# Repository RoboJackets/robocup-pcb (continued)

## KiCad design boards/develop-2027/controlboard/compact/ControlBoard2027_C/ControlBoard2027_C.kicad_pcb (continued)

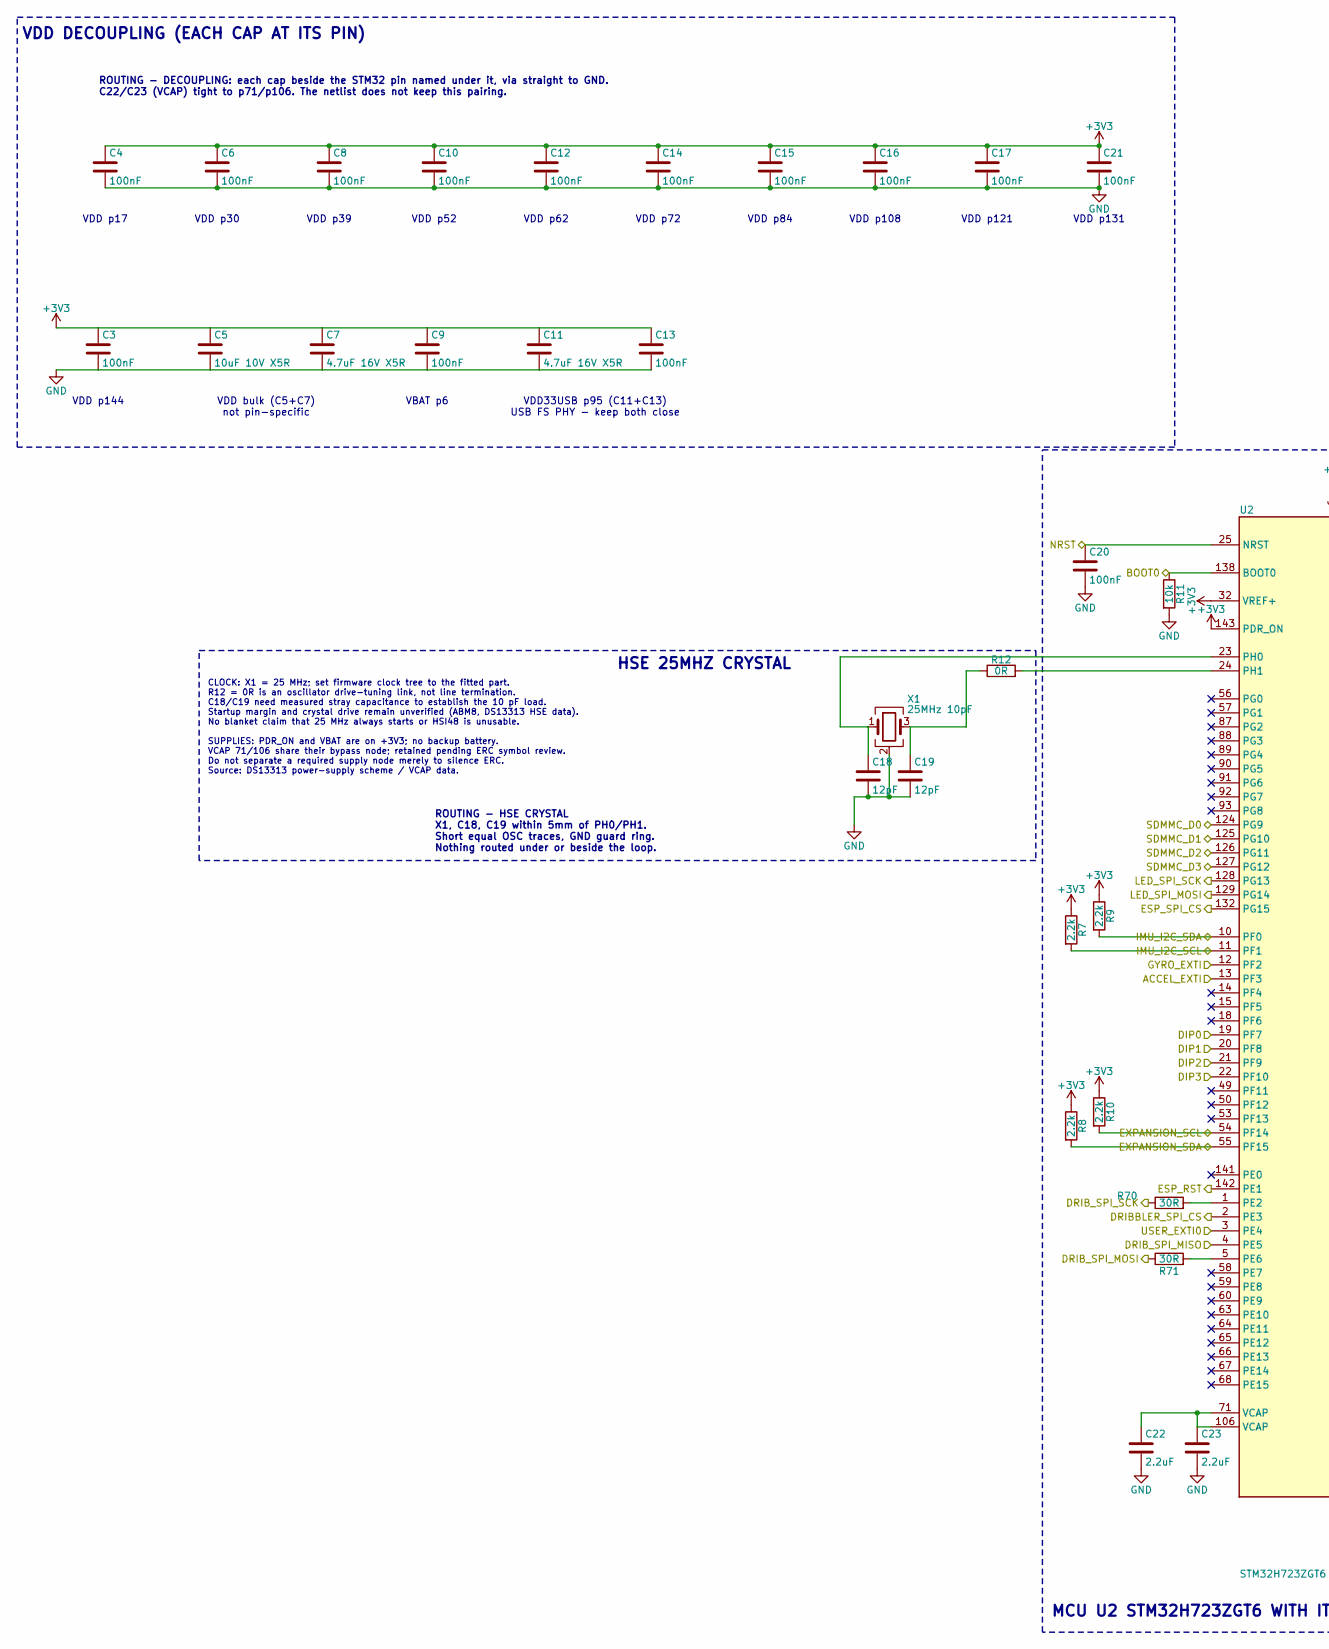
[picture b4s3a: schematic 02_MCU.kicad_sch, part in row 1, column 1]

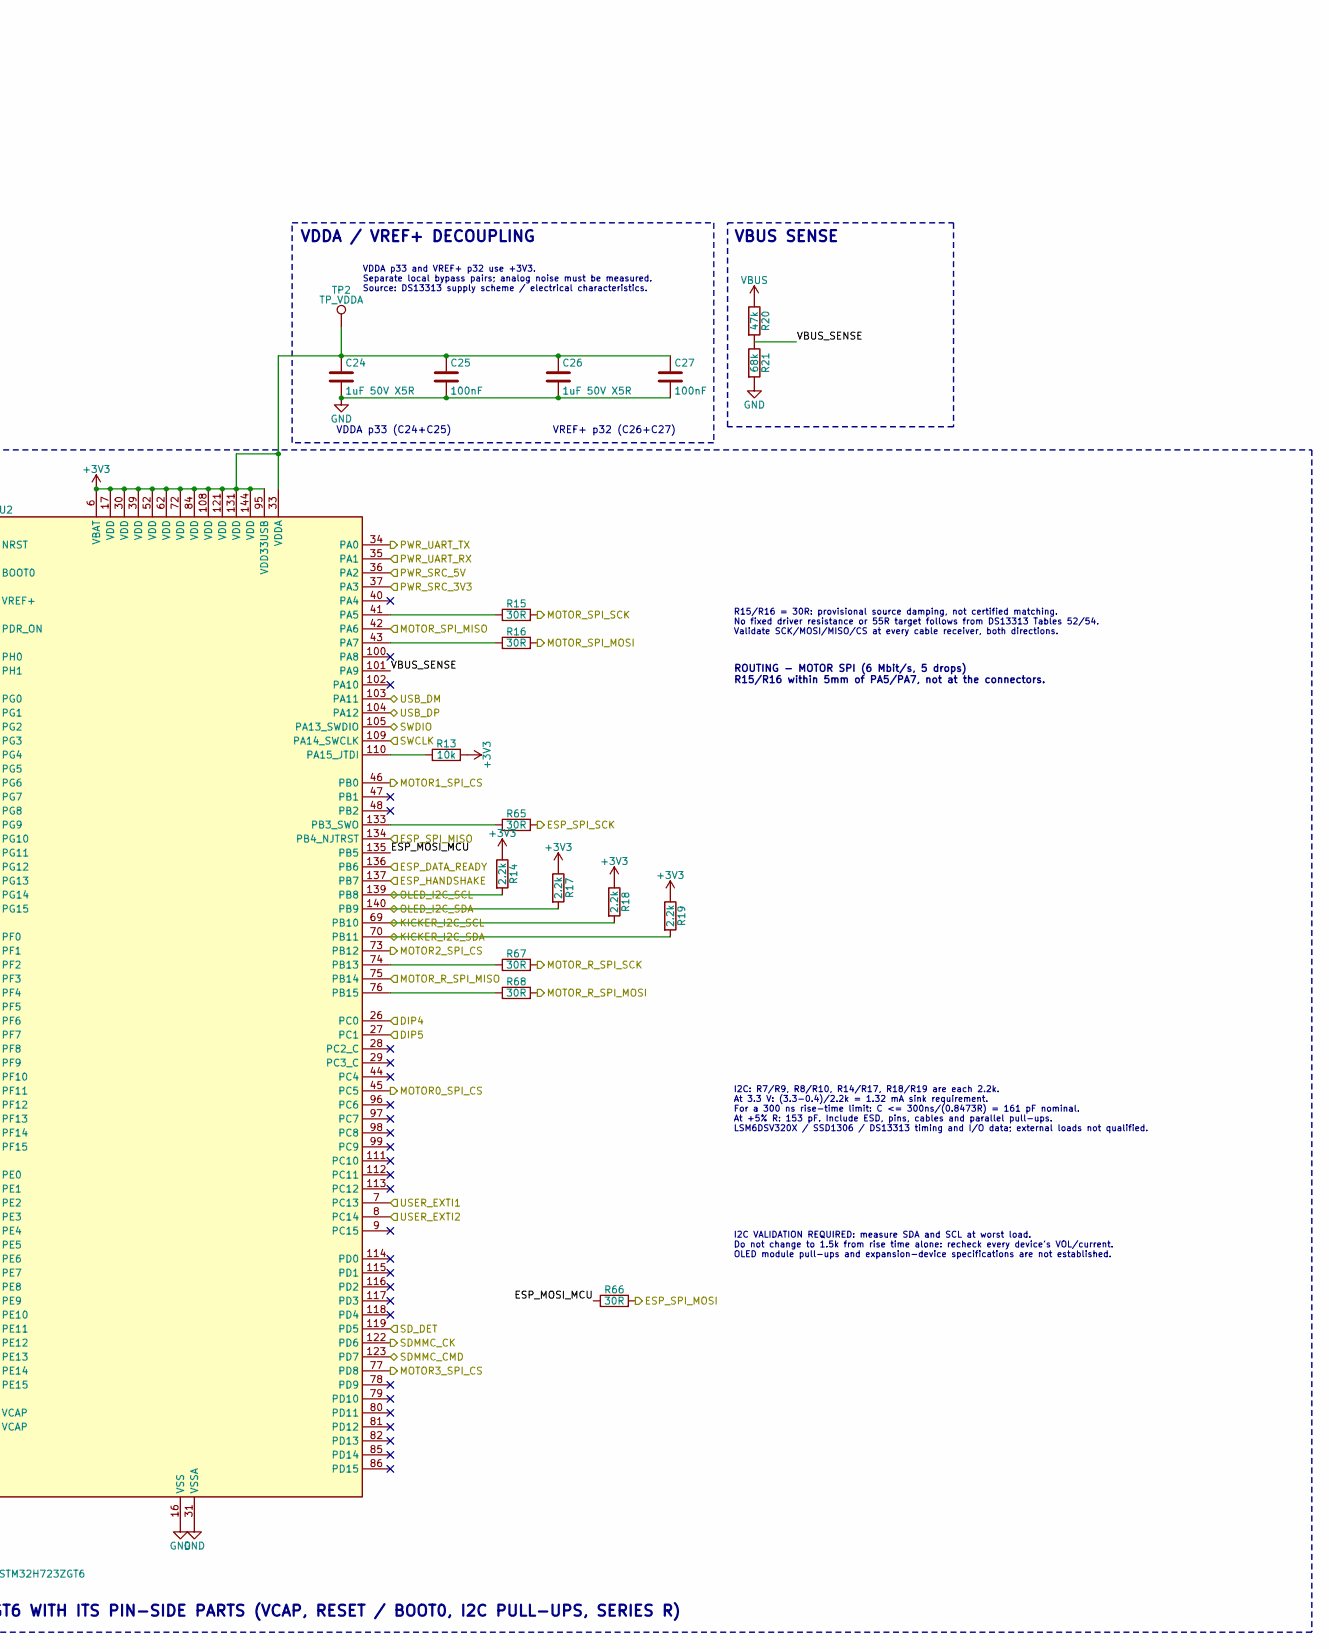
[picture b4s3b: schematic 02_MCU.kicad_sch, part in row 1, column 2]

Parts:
C3, C4, C6, C8, C9, C10, C12, C13, C14, C15, C16, C17, C20, C21, C25, C27: 100nF; C_0402_1005Metric; Rating 16V X7R; MPN Samsung CL05B104KO5NNNC; LCSC C1525
C5: 10uF 10V X5R; C_0603_1608Metric; Rating 10V X5R 10%; MPN Taiyo Yuden LMK107BBJ106MALT; LCSC C19702
C7, C11: 4.7uF 16V X5R; C_0603_1608Metric; Rating 16V X5R; MPN TDK C1608X5R1C475K080AC; LCSC C19666
C18, C19: 12pF; C_0402_1005Metric; Rating 50V C0G; MPN Samsung CL05C120JB5NNNC; LCSC C1547
C22, C23: 2.2uF; C_0603_1608Metric; Rating 10V X7R; MPN Samsung CL10B225KP8NNNC; LCSC C100082
C24, C26: 1uF 50V X5R; C_0603_1608Metric; Rating 50V X5R; MPN Samsung CL10A105KP8NNNC; LCSC C15849
R7, R8, R9, R10, R14, R17, R18, R19: 2.2k; R_0402_1005Metric; Rating 1%; MPN Yageo RC0402FR-072K2L; LCSC C25879
R11, R13: 10k; R_0402_1005Metric; Rating 1%; MPN Yageo RC0402FR-0710KL; LCSC C25744
R12: 0R; R_0402_1005Metric; Rating 0R jumper; MPN Stackpole RMCF0402ZT0R00; LCSC C17168
R15, R16, R65, R66, R67, R68, R70, R71: 30R; R_0402_1005Metric; Rating 1%; MPN Stackpole RMCF0402FT30R0; LCSC C2479340
R20: 47k; R_0402_1005Metric; Rating 1%; MPN Yageo RC0402FR-0747KL; LCSC C25792
R21: 68k; R_0402_1005Metric; Rating 1%; MPN Vishay CRCW040268K0FKED; LCSC C482226
TP2: TP_VDDA; TestPoint_Pad_1.5x1.5mm
U2: STM32H723ZGT6; LQFP-144_20x20mm_P0.5mm; MPN ST STM32H723ZGT6; LCSC C730146
X1: 25MHz 10pF; Crystal_SMD_3225-4Pin_3.2x2.5mm; MPN Abracon ABM8-25.000MHZ-10-B1U-T; LCSC C5366868

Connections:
+3V3: C3.1, C4.1, C5.1, C6.1, C7.1, C8.1, C9.1, C10.1, C11.1, C12.1, C13.1, C14.1, C15.1, C16.1, C17.1, C21.1, C24.1, C25.1, C26.1, C27.1, R7.1, R8.1, R9.1, R10.1, R13.2, R14.1, R17.1, R18.1, R19.1, TP2.1 (1_1), U2.6 (VBAT), U2.17 (VDD), U2.30 (VDD), U2.32 (VREF+), U2.33 (VDDA), U2.39 (VDD), U2.52 (VDD), U2.62 (VDD), U2.72 (VDD), U2.84 (VDD), U2.95 (VDD33USB), U2.108 (VDD), U2.121 (VDD), U2.131 (VDD), U2.143 (PDR_ON), U2.144 (VDD); also elsewhere on the board
/DotStar LEDs/LED_SPI_MOSI: U2.129 (PG14); also elsewhere on the board
/DotStar LEDs/LED_SPI_SCK: U2.128 (PG13); also elsewhere on the board
/IMU/ACCEL_EXTI: U2.13 (PF3); also elsewhere on the board
/IMU/GYRO_EXTI: U2.12 (PF2); also elsewhere on the board
/IMU/IMU_I2C_SCL: R7.2, U2.11 (PF1); also elsewhere on the board
/IMU/IMU_I2C_SDA: R9.2, U2.10 (PF0); also elsewhere on the board
/MCU/BOOT0: R11.1, U2.138 (BOOT0); also elsewhere on the board
/MCU/DIP0: U2.19 (PF7); also elsewhere on the board
/MCU/DIP1: U2.20 (PF8); also elsewhere on the board
/MCU/DIP2: U2.21 (PF9); also elsewhere on the board
/MCU/DIP3: U2.22 (PF10); also elsewhere on the board
/MCU/DIP4: U2.26 (PC0); also elsewhere on the board
/MCU/DIP5: U2.27 (PC1); also elsewhere on the board
/MCU/DRIBBLER_SPI_CS: U2.2 (PE3); also elsewhere on the board
/MCU/DRIB_SPI_MISO: U2.4 (PE5); also elsewhere on the board
/MCU/DRIB_SPI_MOSI: R71.1; also elsewhere on the board
/MCU/DRIB_SPI_SCK: R70.1; also elsewhere on the board
/MCU/ESP_DATA_READY: U2.136 (PB6); also elsewhere on the board
/MCU/ESP_HANDSHAKE: U2.137 (PB7); also elsewhere on the board
/MCU/ESP_MOSI_MCU: R66.1, U2.135 (PB5)
/MCU/ESP_RST: U2.142 (PE1); also elsewhere on the board
/MCU/ESP_SPI_CS: U2.132 (PG15); also elsewhere on the board
/MCU/ESP_SPI_MISO: U2.134 (PB4_NJTRST); also elsewhere on the board
/MCU/ESP_SPI_MOSI: R66.2; also elsewhere on the board
/MCU/ESP_SPI_SCK: R65.2; also elsewhere on the board
/MCU/EXPANSION_SCL: R10.2, U2.54 (PF14); also elsewhere on the board
/MCU/EXPANSION_SDA: R8.2, U2.55 (PF15); also elsewhere on the board
/MCU/KICKER_I2C_SCL: R18.2, U2.69 (PB10); also elsewhere on the board
/MCU/KICKER_I2C_SDA: R19.2, U2.70 (PB11); also elsewhere on the board
/MCU/MOTOR0_SPI_CS: U2.45 (PC5); also elsewhere on the board
/MCU/MOTOR1_SPI_CS: U2.46 (PB0); also elsewhere on the board
/MCU/MOTOR2_SPI_CS: U2.73 (PB12); also elsewhere on the board
/MCU/MOTOR3_SPI_CS: U2.77 (PD8); also elsewhere on the board
/MCU/MOTOR_R_SPI_MISO: U2.75 (PB14); also elsewhere on the board
/MCU/MOTOR_R_SPI_MOSI: R68.2; also elsewhere on the board
/MCU/MOTOR_R_SPI_SCK: R67.2; also elsewhere on the board
/MCU/MOTOR_SPI_MISO: U2.42 (PA6); also elsewhere on the board
/MCU/MOTOR_SPI_MOSI: R16.2; also elsewhere on the board
/MCU/MOTOR_SPI_SCK: R15.2; also elsewhere on the board
/MCU/NRST: C20.1, U2.25 (NRST); also elsewhere on the board
/MCU/OLED_I2C_SCL: R14.2, U2.139 (PB8); also elsewhere on the board
/MCU/OLED_I2C_SDA: R17.2, U2.140 (PB9); also elsewhere on the board
/MCU/PWR_SRC_3V3: U2.37 (PA3); also elsewhere on the board
/MCU/PWR_SRC_5V: U2.36 (PA2); also elsewhere on the board
/MCU/PWR_UART_RX: U2.35 (PA1); also elsewhere on the board
/MCU/PWR_UART_TX: U2.34 (PA0); also elsewhere on the board
/MCU/SDMMC_CK: U2.122 (PD6); also elsewhere on the board
/MCU/SD_DET: U2.119 (PD5); also elsewhere on the board
/MCU/SWCLK: U2.109 (PA14_SWCLK); also elsewhere on the board
/MCU/SWDIO: U2.105 (PA13_SWDIO); also elsewhere on the board
/MCU/USER_EXTI0: U2.3 (PE4); also elsewhere on the board
/MCU/USER_EXTI1: U2.7 (PC13); also elsewhere on the board
/MCU/USER_EXTI2: U2.8 (PC14); also elsewhere on the board
/MCU/VBUS_SENSE: R20.2, R21.1, U2.101 (PA9)
/SD Card Storage/SDMMC_CMD: U2.123 (PD7); also elsewhere on the board
/SD Card Storage/SDMMC_D0: U2.124 (PG9); also elsewhere on the board
/SD Card Storage/SDMMC_D1: U2.125 (PG10); also elsewhere on the board
/SD Card Storage/SDMMC_D2: U2.126 (PG11); also elsewhere on the board
/SD Card Storage/SDMMC_D3: U2.127 (PG12); also elsewhere on the board
/USB and Debug/USB_DM: U2.103 (PA11); also elsewhere on the board
/USB and Debug/USB_DP: U2.104 (PA12); also elsewhere on the board
unnamed: C19.1, R12.1, X1.3
unnamed: C22.1, C23.1, U2.71 (VCAP), U2.106 (VCAP)
unnamed: R15.1, U2.41 (PA5)
unnamed: R16.1, U2.43 (PA7)
unnamed: R13.1, U2.110 (PA15_JTDI)
unnamed: R65.1, U2.133 (PB3_SWO)
unnamed: R67.1, U2.74 (PB13)
unnamed: R68.1, U2.76 (PB15)
unnamed: R70.2, U2.1 (PE2)
unnamed: R71.2, U2.5 (PE6)
unnamed: C18.1, U2.23 (PH0), X1.1
unnamed: R12.2, U2.24 (PH1)
VBUS: R20.1; also elsewhere on the board

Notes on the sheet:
VDD33USB p95 (C11+C13) USB FS PHY - keep both close
VDD p30
VBUS SENSE
MCU U2 STM32H723ZGT6 WITH ITS PIN-SIDE PARTS (VCAP, RESET / BOOT0, I2C PULL-UPS, SERIES R)
VDD p17
VDDA p33 (C24+C25)
VDD p131
HSE 25MHZ CRYSTAL
CLOCK: X1 = 25 MHz; set firmware clock tree to the fitted part. R12 = 0R is an oscillator drive-tuning link, not line termination. C18/C19 need measured stray capacitance to establish the 10 pF load. Startup margin and crystal drive remain unverified (ABM8, DS13313 HSE data). No blanket claim that 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
R15/R16 = 30R: provisional source damping, not certified matching. No fixed driver resistance or 55R target follows from DS13313 Tables 52/54. Validate SCK/MOSI/MISO/CS at every cable receiver, both directions.
VDD p84
VDDA p33 and VREF+ p32 use +3V3. Separate local bypass pairs; analog noise must be measured. Source: DS13313 supply scheme / electrical characteristics.
VDD p52
VBAT p6
VREF+ p32 (C26+C27)
VDD DECOUPLING (EACH CAP AT ITS PIN)
VDD p39
VDD p62
VDDA / VREF+ DECOUPLING
ROUTING - HSE CRYSTAL X1, C18, C19 within 5mm of PH0/PH1. Short equal OSC traces, GND guard ring. Nothing routed under or beside the loop.
I2C: R7/R9, R8/R10, R14/R17, R18/R19 are each 2.2k. At 3.3 V: (3.3-0.4)/2.2k = 1.32 mA sink requirement. For a 300 ns rise-time limit: C <= 300ns/(0.8473R) = 161 pF nominal. At +5% R: 153 pF. Include ESD, pins, cables and parallel pull-ups. LSM6DSV320X / SSD1306 / DS13313 timing and I/O data; exter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
VDD p108
ROUTING - DECOUPLING: each cap beside the STM32 pin named under it, via straight to GND. C22/C23 (VCAP) tight to p71/p106. The netlist does not keep this pairing.
VDD bulk (C5+C7) not pin-specific
ROUTING - MOTOR SPI (6 Mbit/s, 5 drops) R15/R16 within 5mm of PA5/PA7, not at the connectors.
I2C VALIDATION REQUIRED: measure SDA and SCL at worst load. Do not change to 1.5k from rise time alone: recheck every device's VOL/current. OLED module pull-ups and expansion-device specifications are not established.
VDD p72
VDD p121
VDD p144

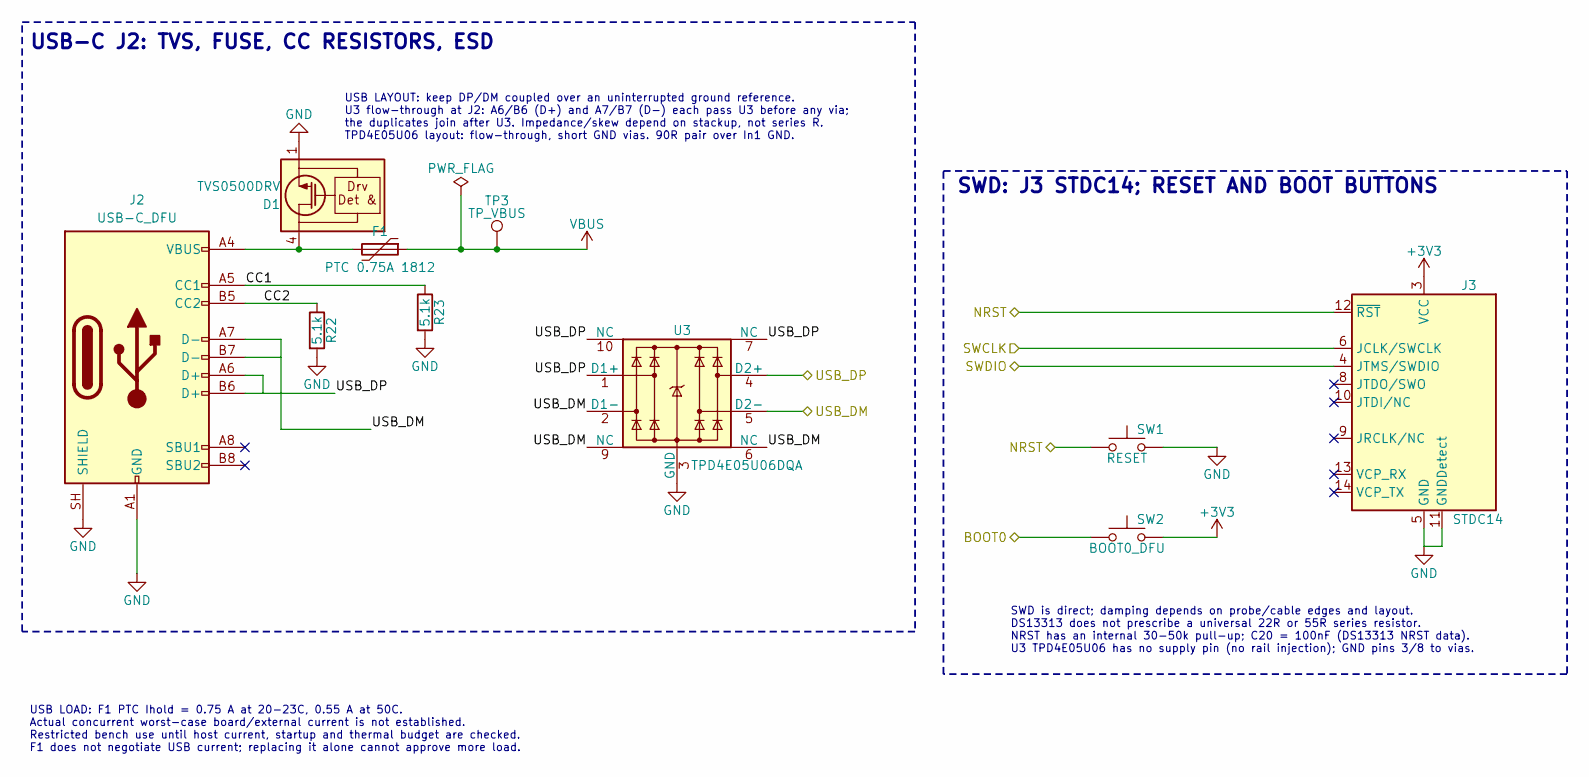
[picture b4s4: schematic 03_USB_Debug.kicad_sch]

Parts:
D1: TVS0500DRV; WSON-6-1EP_2x2mm_P0.65mm_EP1x1.6mm; MPN TI TVS0500DRVR; LCSC C609571
F1: PTC 0.75A 1812; Fuse_Bourns_MF-MSMF_1812; MPN Bourns MF-MSMF075/16X-2; LCSC C207065
J2: USB-C_DFU; USB_C_Receptacle_GCT_USB4110; MPN GCT USB4110-GF-A; LCSC C5143397
J3: STDC14; PinHeader_2x07_P1.27mm_Vertical_SMD; MPN Samtec FTSH-107-01-L-DV-K; LCSC C5307809
R22, R23: 5.1k; R_0402_1005Metric; Rating 1%; MPN Yageo RC0402FR-075K1L; LCSC C25905
SW1: RESET; SW_PUSH_1P1T_6x3.5mm_H4.3_APEM_MJTP1243; MPN APEM MJTP1243; LCSC C2689636
SW2: BOOT0_DFU; SW_PUSH_1P1T_6x3.5mm_H4.3_APEM_MJTP1243; MPN APEM MJTP1243; LCSC C2689636
TP3: TP_VBUS; TestPoint_Pad_1.5x1.5mm
U3: TPD4E05U06DQA; USON-10_2.5x1.0mm_P0.5mm; MPN TI TPD4E05U06DQAR; LCSC C138714

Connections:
+3V3: J3.3 (VCC), SW2.2; also elsewhere on the board
/MCU/BOOT0: SW2.1; also elsewhere on the board
/MCU/NRST: J3.12 (~RST), SW1.1; also elsewhere on the board
/MCU/SWCLK: J3.6 (JCLK/SWCLK); also elsewhere on the board
/MCU/SWDIO: J3.4 (JTMS/SWDIO); also elsewhere on the board
/USB and Debug/CC1: J2.A5 (CC1), R23.1
/USB and Debug/CC2: J2.B5 (CC2), R22.1
/USB and Debug/USB_DM: J2.A7 (D-), J2.B7 (D-), U3.2 (D1-), U3.5 (D2-), U3.6 (NC), U3.9 (NC); also elsewhere on the board
/USB and Debug/USB_DP: J2.A6 (D+), J2.B6 (D+), U3.1 (D1+), U3.4 (D2+), U3.7 (NC), U3.10 (NC); also elsewhere on the board
unnamed: D1.4 (IN), D1.5 (IN), D1.6 (IN), F1.2, J2.A4 (VBUS), J2.A9 (VBUS), J2.B4 (VBUS), J2.B9 (VBUS)
VBUS: F1.1, TP3.1 (1_1); also elsewhere on the board

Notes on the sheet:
USB LOAD: F1 PTC Ihold = 0.75 A at 20-23C, 0.55 A at 50C. Actual concurrent worst-case board/external current is not established. Restricted bench use until host current, startup and thermal budget are checked. F1 does not negotiate USB current; replacing it alone cannot approve more load.
USB-C J2: TVS, FUSE, CC RESISTORS, ESD
SWD is direct; damping depends on probe/cable edges and layout. DS13313 does not prescribe a universal 22R or 55R series resistor. NRST has an internal 30-50k pull-up; C20 = 100nF (DS13313 NRST data). U3 TPD4E05U06 has no supply pin (no rail injection); GND pins 3/8 to vias.
SWD: J3 STDC14; RESET AND BOOT BUTTONS
USB LAYOUT: keep DP/DM coupled over an uninterrupted ground reference. U3 flow-through at J2: A6/B6 (D+) and A7/B7 (D-) each pass U3 before any via; the duplicates join after U3. Impedance/skew depend on stackup, not series R. TPD4E05U06 layout: flow-through, short GND vias. 90R pair over In1 GND.

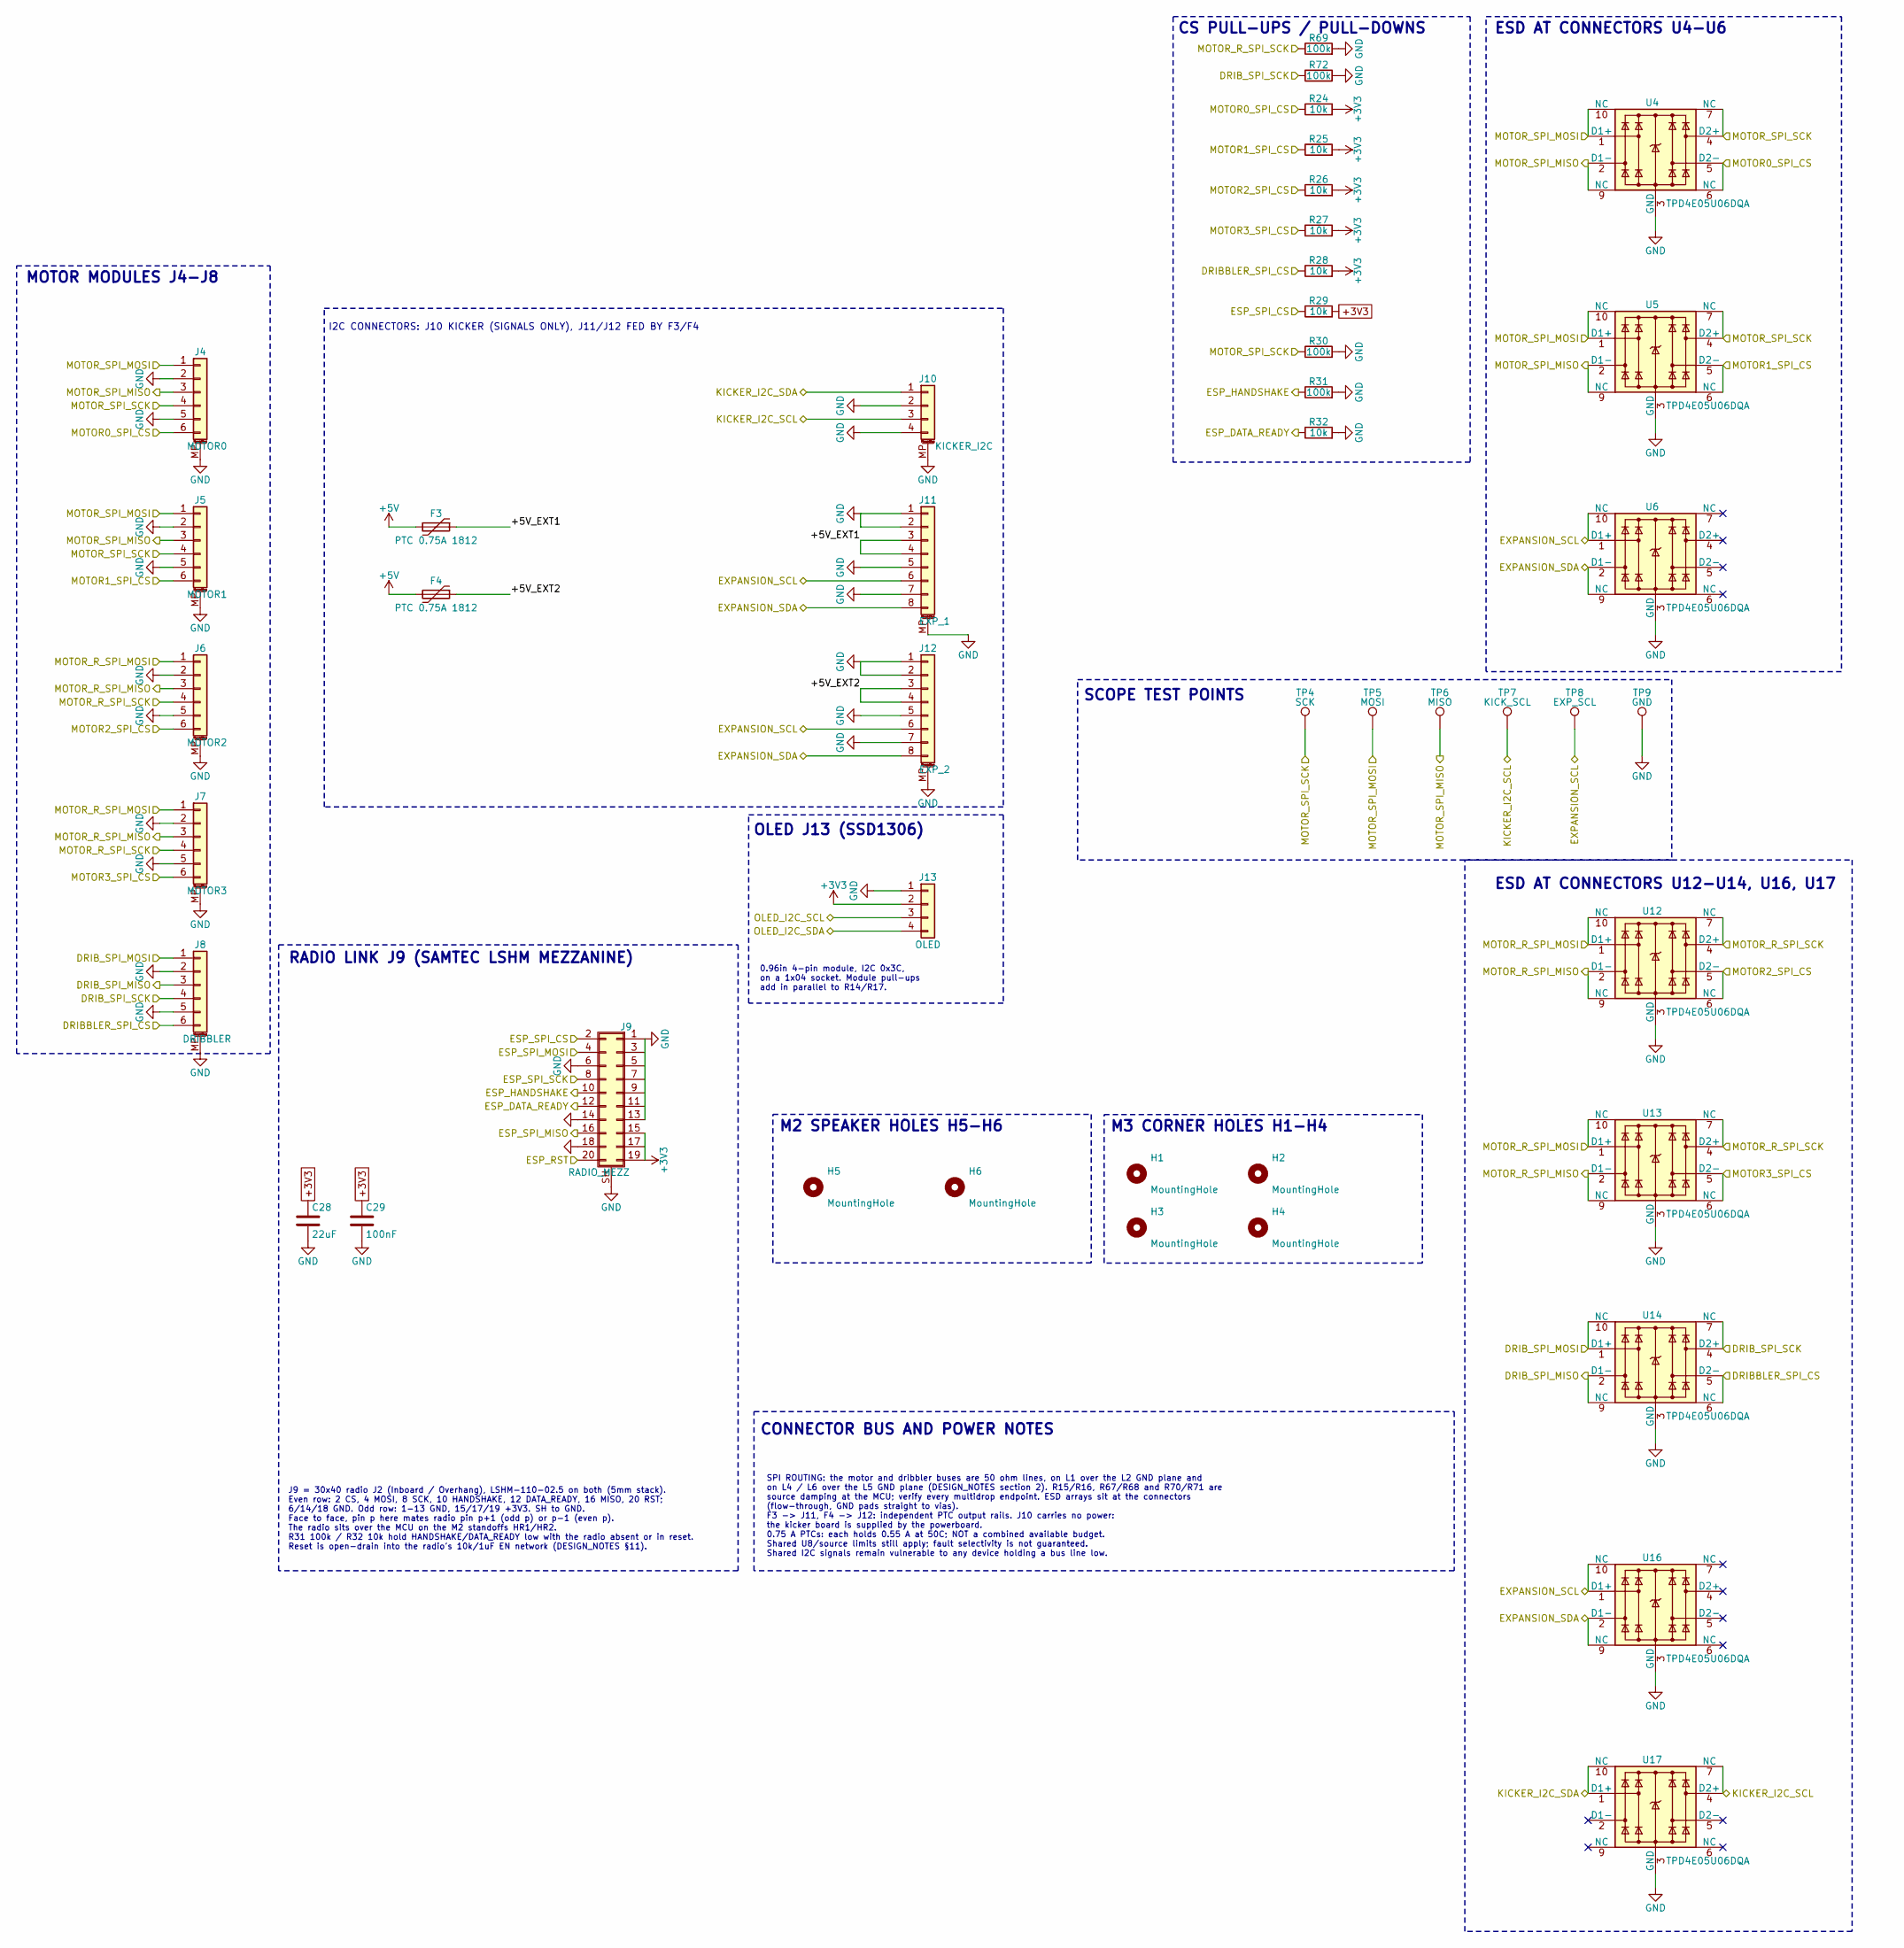
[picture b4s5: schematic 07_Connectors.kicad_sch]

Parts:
C28: 22uF; C_0805_2012Metric; Rating 25V X5R 20%; MPN Samsung CL21A226MOQNNNE; LCSC C45783
C29: 100nF; C_0402_1005Metric; Rating 16V X7R; MPN Samsung CL05B104KO5NNNC; LCSC C1525
F3, F4: PTC 0.75A 1812; Fuse_Bourns_MF-MSMF_1812; MPN Bourns MF-MSMF075/16X-2; LCSC C207065
H1, H2, H3, H4: MountingHole; MountingHole_3.2mm_M3
H5, H6: MountingHole; MountingHole_2.2mm_M2
J4: MOTOR0; JST_GH_SM06B-GHS-TB_1x06-1MP_P1.25mm_Horizontal; MPN JST SM06B-GHS-TB(LF)(SN); LCSC C133065
J5: MOTOR1; JST_GH_SM06B-GHS-TB_1x06-1MP_P1.25mm_Horizontal; MPN JST SM06B-GHS-TB(LF)(SN); LCSC C133065
J6: MOTOR2; JST_GH_SM06B-GHS-TB_1x06-1MP_P1.25mm_Horizontal; MPN JST SM06B-GHS-TB(LF)(SN); LCSC C133065
J7: MOTOR3; JST_GH_SM06B-GHS-TB_1x06-1MP_P1.25mm_Horizontal; MPN JST SM06B-GHS-TB(LF)(SN); LCSC C133065
J8: DRIBBLER; JST_GH_SM06B-GHS-TB_1x06-1MP_P1.25mm_Horizontal; MPN JST SM06B-GHS-TB(LF)(SN); LCSC C133065
J9: RADIO_MEZZ; Samtec_LSHM-110-xx.x-x-DV-S_2x10-1SH_P0.50mm_Vertical_PIH; MPN Samtec LSHM-110-02.5-L-DV-A-S-K-TR; LCSC C3643542
J10: KICKER_I2C; JST_GH_SM04B-GHS-TB_1x04-1MP_P1.25mm_Horizontal; MPN JST SM04B-GHS-TB(LF)(SN); LCSC C189895
J11: EXP_1; JST_GH_SM08B-GHS-TB_1x08-1MP_P1.25mm_Horizontal; MPN JST SM08B-GHS-TB(LF)(SN); LCSC C265111
J12: EXP_2; JST_GH_SM08B-GHS-TB_1x08-1MP_P1.25mm_Horizontal; MPN JST SM08B-GHS-TB(LF)(SN); LCSC C265111
J13: OLED; OLED_0.96in_SSD1306_I2C_Module_Socket_1x04_P2.54mm; MPN BOOMELE 2.54-1*4P; LCSC C2718488
R24, R25, R26, R27, R28, R29, R32: 10k; R_0402_1005Metric; Rating 1%; MPN Yageo RC0402FR-0710KL; LCSC C25744
R30, R31, R69, R72: 100k; R_0402_1005Metric; Rating 1%; MPN Yageo RC0402FR-07100KL; LCSC C25741
TP4: SCK; TestPoint_Pad_1.5x1.5mm
TP5: MOSI; TestPoint_Pad_1.5x1.5mm
TP6: MISO; TestPoint_Pad_D1.0mm
TP7: KICK_SCL; TestPoint_Pad_1.5x1.5mm
TP8: EXP_SCL; TestPoint_Pad_1.5x1.5mm
TP9: GND; TestPoint_Pad_1.5x1.5mm
U4, U5, U6, U12, U13, U14, U16, U17: TPD4E05U06DQA; USON-10_2.5x1.0mm_P0.5mm; MPN TI TPD4E05U06DQAR; LCSC C138714

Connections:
+3V3: C28.1, C29.1, J9.15, J9.17, J9.19, J13.2, R24.2, R25.2, R26.2, R27.2, R28.2, R29.2; also elsewhere on the board
+5V: F3.2, F4.2; also elsewhere on the board
/MCU/DRIBBLER_SPI_CS: J8.6, R28.1, U14.5 (D2-), U14.6 (NC); also elsewhere on the board
/MCU/DRIB_SPI_MISO: J8.3, U14.2 (D1-), U14.9 (NC); also elsewhere on the board
/MCU/DRIB_SPI_MOSI: J8.1, U14.1 (D1+), U14.10 (NC); also elsewhere on the board
/MCU/DRIB_SPI_SCK: J8.4, R72.1, U14.4 (D2+), U14.7 (NC); also elsewhere on the board
/MCU/ESP_DATA_READY: J9.12, R32.1; also elsewhere on the board
/MCU/ESP_HANDSHAKE: J9.10, R31.1; also elsewhere on the board
/MCU/ESP_RST: J9.20; also elsewhere on the board
/MCU/ESP_SPI_CS: J9.2, R29.1; also elsewhere on the board
/MCU/ESP_SPI_MISO: J9.16; also elsewhere on the board
/MCU/ESP_SPI_MOSI: J9.4; also elsewhere on the board
/MCU/ESP_SPI_SCK: J9.8; also elsewhere on the board
/MCU/EXPANSION_SCL: J11.6, J12.6, TP8.1 (1_1), U6.1 (D1+), U6.10 (NC), U16.1 (D1+), U16.10 (NC); also elsewhere on the board
/MCU/EXPANSION_SDA: J11.8, J12.8, U6.2 (D1-), U6.9 (NC), U16.2 (D1-), U16.9 (NC); also elsewhere on the board
/MCU/KICKER_I2C_SCL: J10.3, TP7.1 (1_1), U17.4 (D2+), U17.7 (NC); also elsewhere on the board
/MCU/KICKER_I2C_SDA: J10.1, U17.1 (D1+), U17.10 (NC); also elsewhere on the board
/MCU/MOTOR0_SPI_CS: J4.6, R24.1, U4.5 (D2-), U4.6 (NC); also elsewhere on the board
/MCU/MOTOR1_SPI_CS: J5.6, R25.1, U5.5 (D2-), U5.6 (NC); also elsewhere on the board
/MCU/MOTOR2_SPI_CS: J6.6, R26.1, U12.5 (D2-), U12.6 (NC); also elsewhere on the board
/MCU/MOTOR3_SPI_CS: J7.6, R27.1, U13.5 (D2-), U13.6 (NC); also elsewhere on the board
/MCU/MOTOR_R_SPI_MISO: J6.3, J7.3, U12.2 (D1-), U12.9 (NC), U13.2 (D1-), U13.9 (NC); also elsewhere on the board
/MCU/MOTOR_R_SPI_MOSI: J6.1, J7.1, U12.1 (D1+), U12.10 (NC), U13.1 (D1+), U13.10 (NC); also elsewhere on the board
/MCU/MOTOR_R_SPI_SCK: J6.4, J7.4, R69.1, U12.4 (D2+), U12.7 (NC), U13.4 (D2+), U13.7 (NC); also elsewhere on the board
/MCU/MOTOR_SPI_MISO: J4.3, J5.3, TP6.1 (1_1), U4.2 (D1-), U4.9 (NC), U5.2 (D1-), U5.9 (NC); also elsewhere on the board
/MCU/MOTOR_SPI_MOSI: J4.1, J5.1, TP5.1 (1_1), U4.1 (D1+), U4.10 (NC), U5.1 (D1+), U5.10 (NC); also elsewhere on the board
/MCU/MOTOR_SPI_SCK: J4.4, J5.4, R30.1, TP4.1 (1_1), U4.4 (D2+), U4.7 (NC), U5.4 (D2+), U5.7 (NC); also elsewhere on the board
/MCU/OLED_I2C_SCL: J13.3; also elsewhere on the board
/MCU/OLED_I2C_SDA: J13.4; also elsewhere on the board
/Motor, Kicker, Expansion, OLED, Radio/+5V_EXT1: F3.1, J11.3, J11.4
/Motor, Kicker, Expansion, OLED, Radio/+5V_EXT2: F4.1, J12.3, J12.4

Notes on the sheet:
0.96in 4-pin module, I2C 0x3C, on a 1x04 socket. Module pull-ups add in parallel to R14/R17.
ESD AT CONNECTORS U4-U6
M2 SPEAKER HOLES H5-H6
M3 CORNER HOLES H1-H4
SPI ROUTING: the motor and dribbler buses are 50 ohm lines, on L1 over the L2 GND plane and on L4 / L6 over the L5 GND plane (DESIGN_NOTES section 2). R15/R16, R67/R68 and R70/R71 are source damping at the MCU; verify every multidrop endpoint. ESD arrays sit at the connectors (flow-through, GND pad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
J9 = 30x40 radio J2 (Inboard / Overhang), LSHM-110-02.5 on both (5mm stack). Even row: 2 CS, 4 MOSI, 8 SCK, 10 HANDSHAKE, 12 DATA_READY, 16 MISO, 20 RST; 6/14/18 GND. Odd row: 1-13 GND, 15/17/19 +3V3. SH to GND. Face to face, pin p here mates radio pin p+1 (odd p) or p-1 (even p). The radio sits ov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
CS PULL-UPS / PULL-DOWNS
MOTOR MODULES J4-J8
OLED J13 (SSD1306)
I2C CONNECTORS: J10 KICKER (SIGNALS ONLY), J11/J12 FED BY F3/F4
RADIO LINK J9 (SAMTEC LSHM MEZZANINE)
ESD AT CONNECTORS U12-U14, U16, U17
SCOPE TEST POINTS
CONNECTOR BUS AND POWER NOTES
